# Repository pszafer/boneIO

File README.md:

# Project description

`BoneIO` is a compact IO controller for home automation. Main features of this controller are

- Compact size (27x11x6)cm - 15 DIN modules
- DIN rail compatibility
- Low price
- Open HSP (See below)

## Whole documentation you will find here: https://boneio.eu/

## Case, Circuit and Code was moved into separate repositories. You can find it here: https://github.com/boneIO-eu

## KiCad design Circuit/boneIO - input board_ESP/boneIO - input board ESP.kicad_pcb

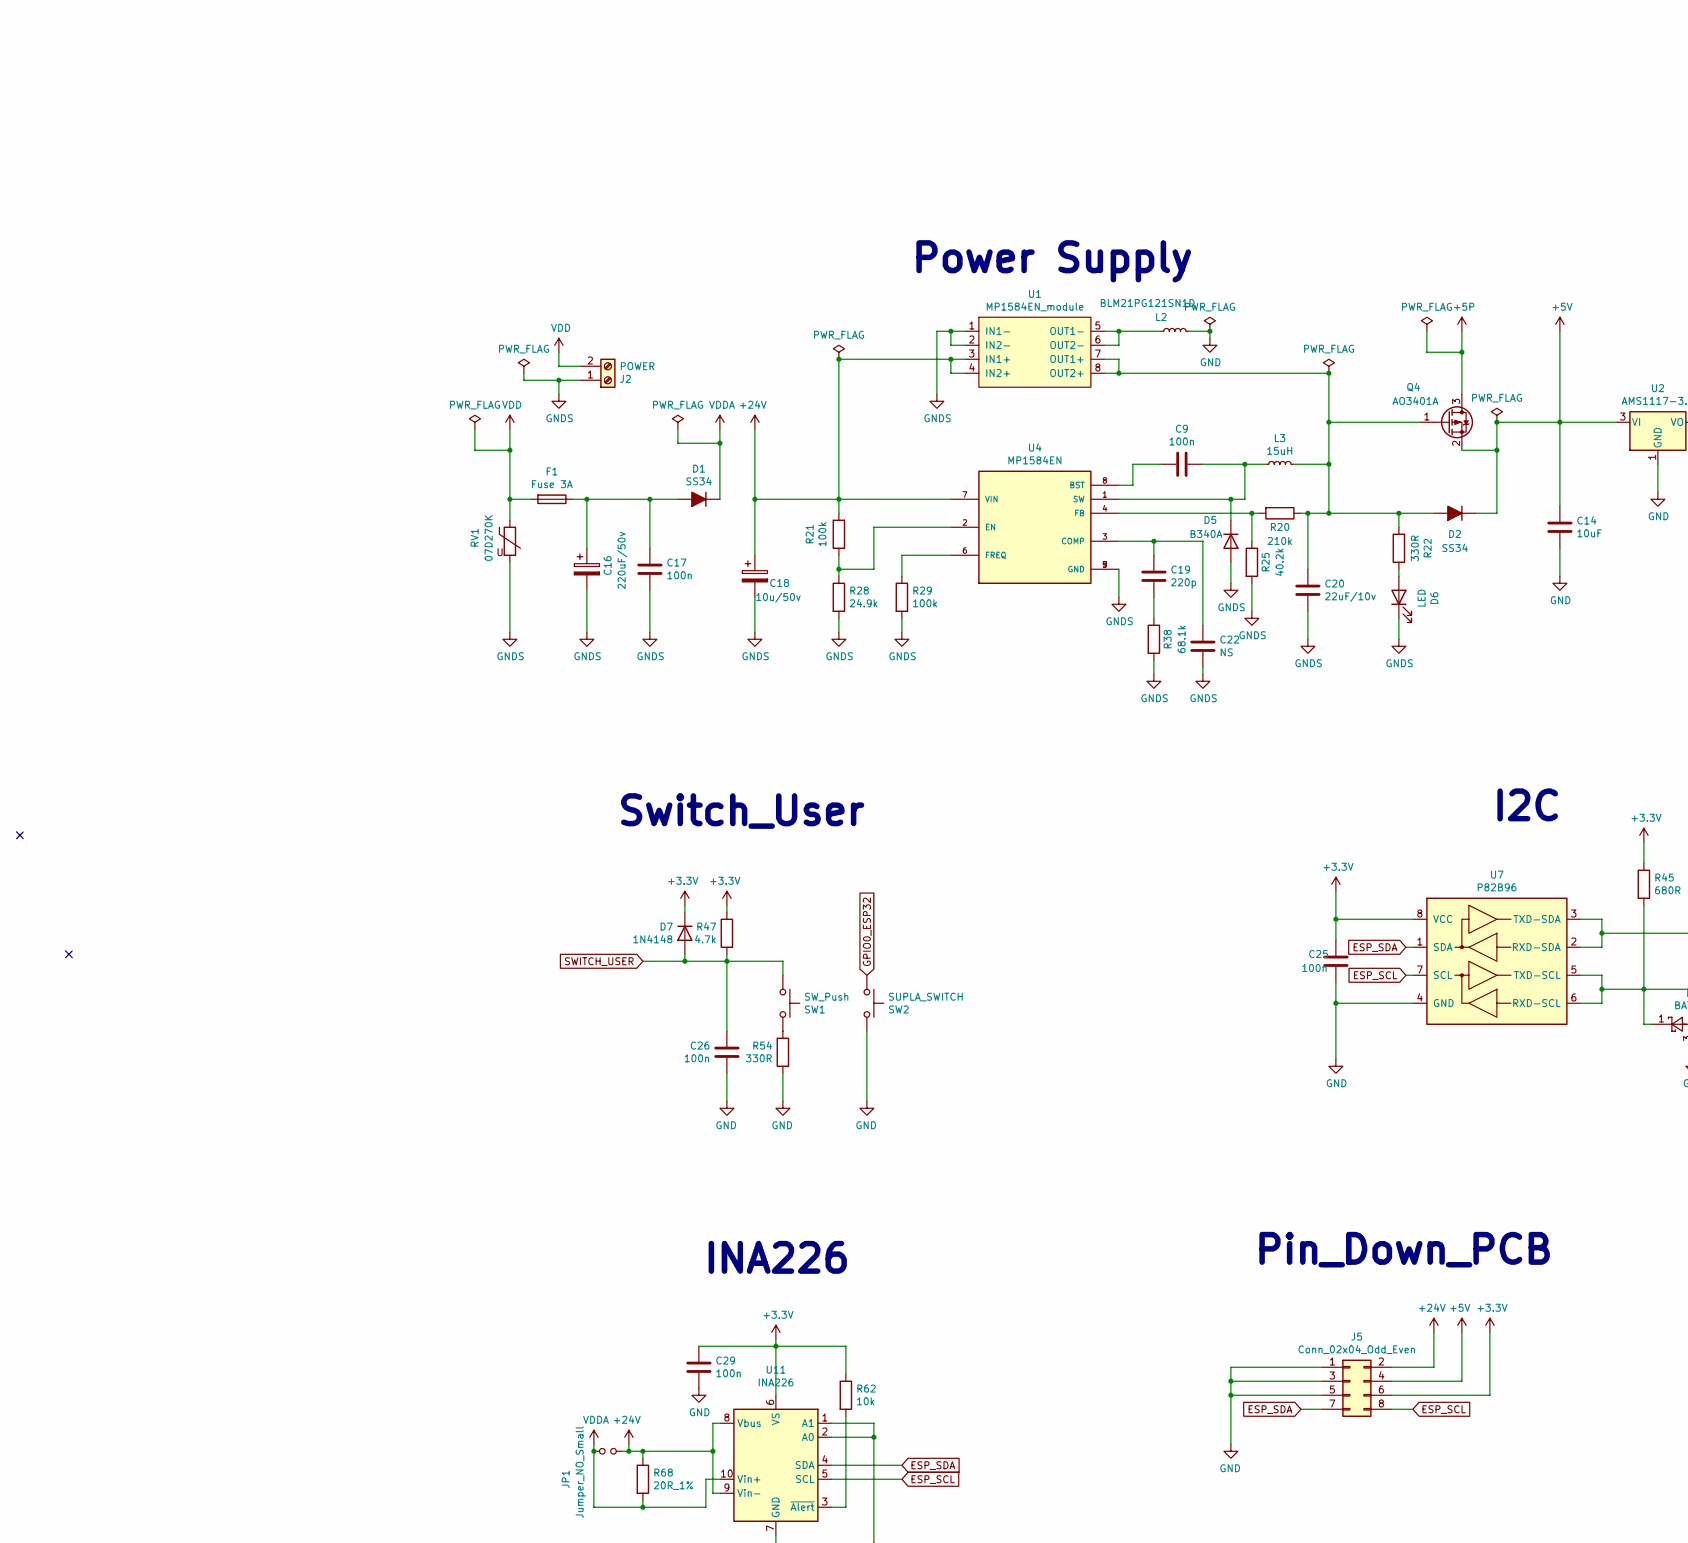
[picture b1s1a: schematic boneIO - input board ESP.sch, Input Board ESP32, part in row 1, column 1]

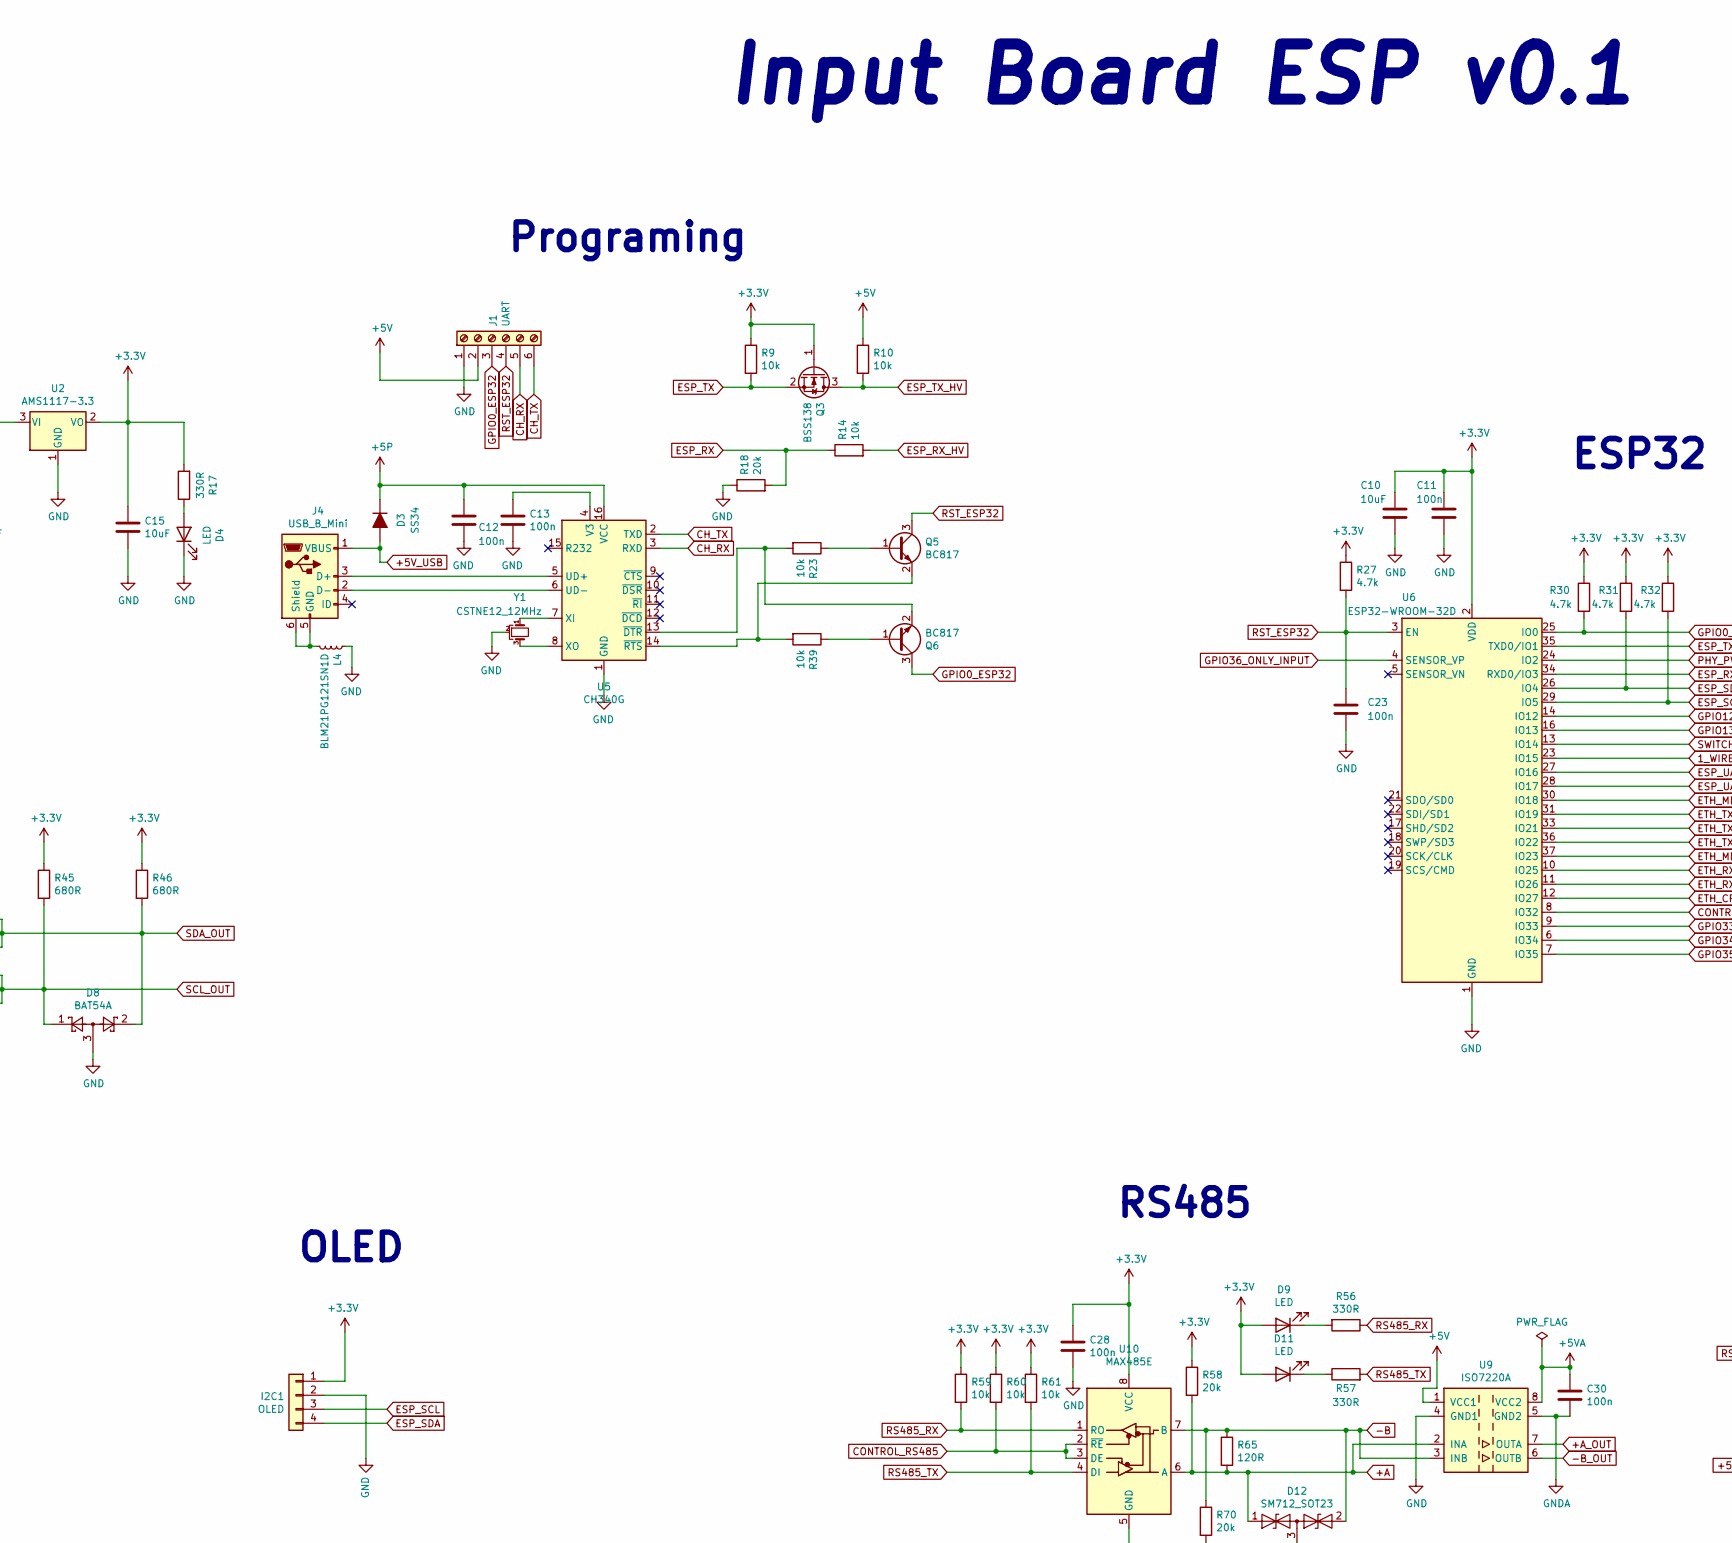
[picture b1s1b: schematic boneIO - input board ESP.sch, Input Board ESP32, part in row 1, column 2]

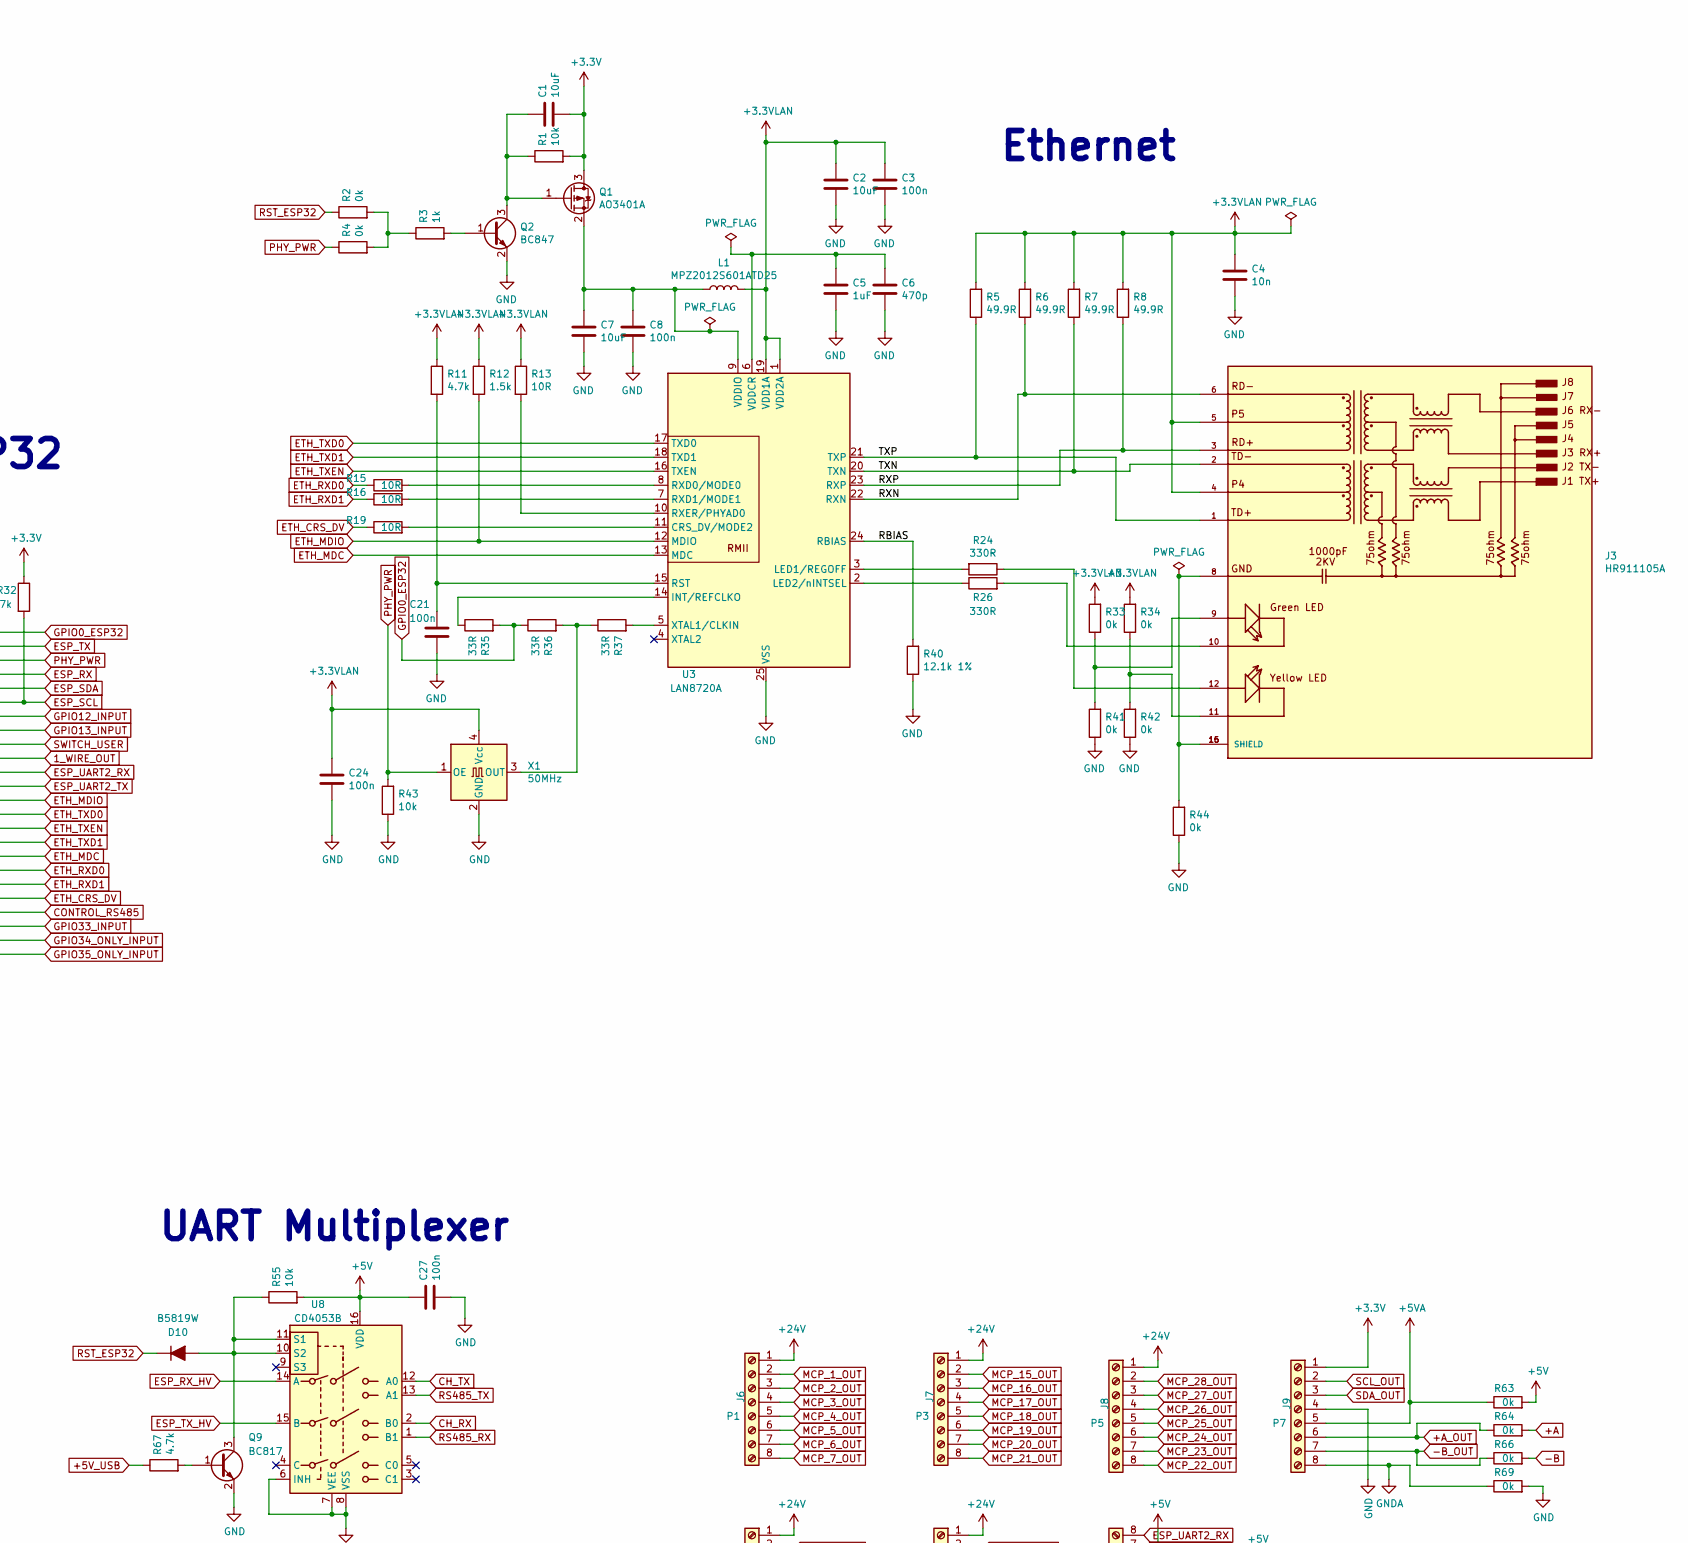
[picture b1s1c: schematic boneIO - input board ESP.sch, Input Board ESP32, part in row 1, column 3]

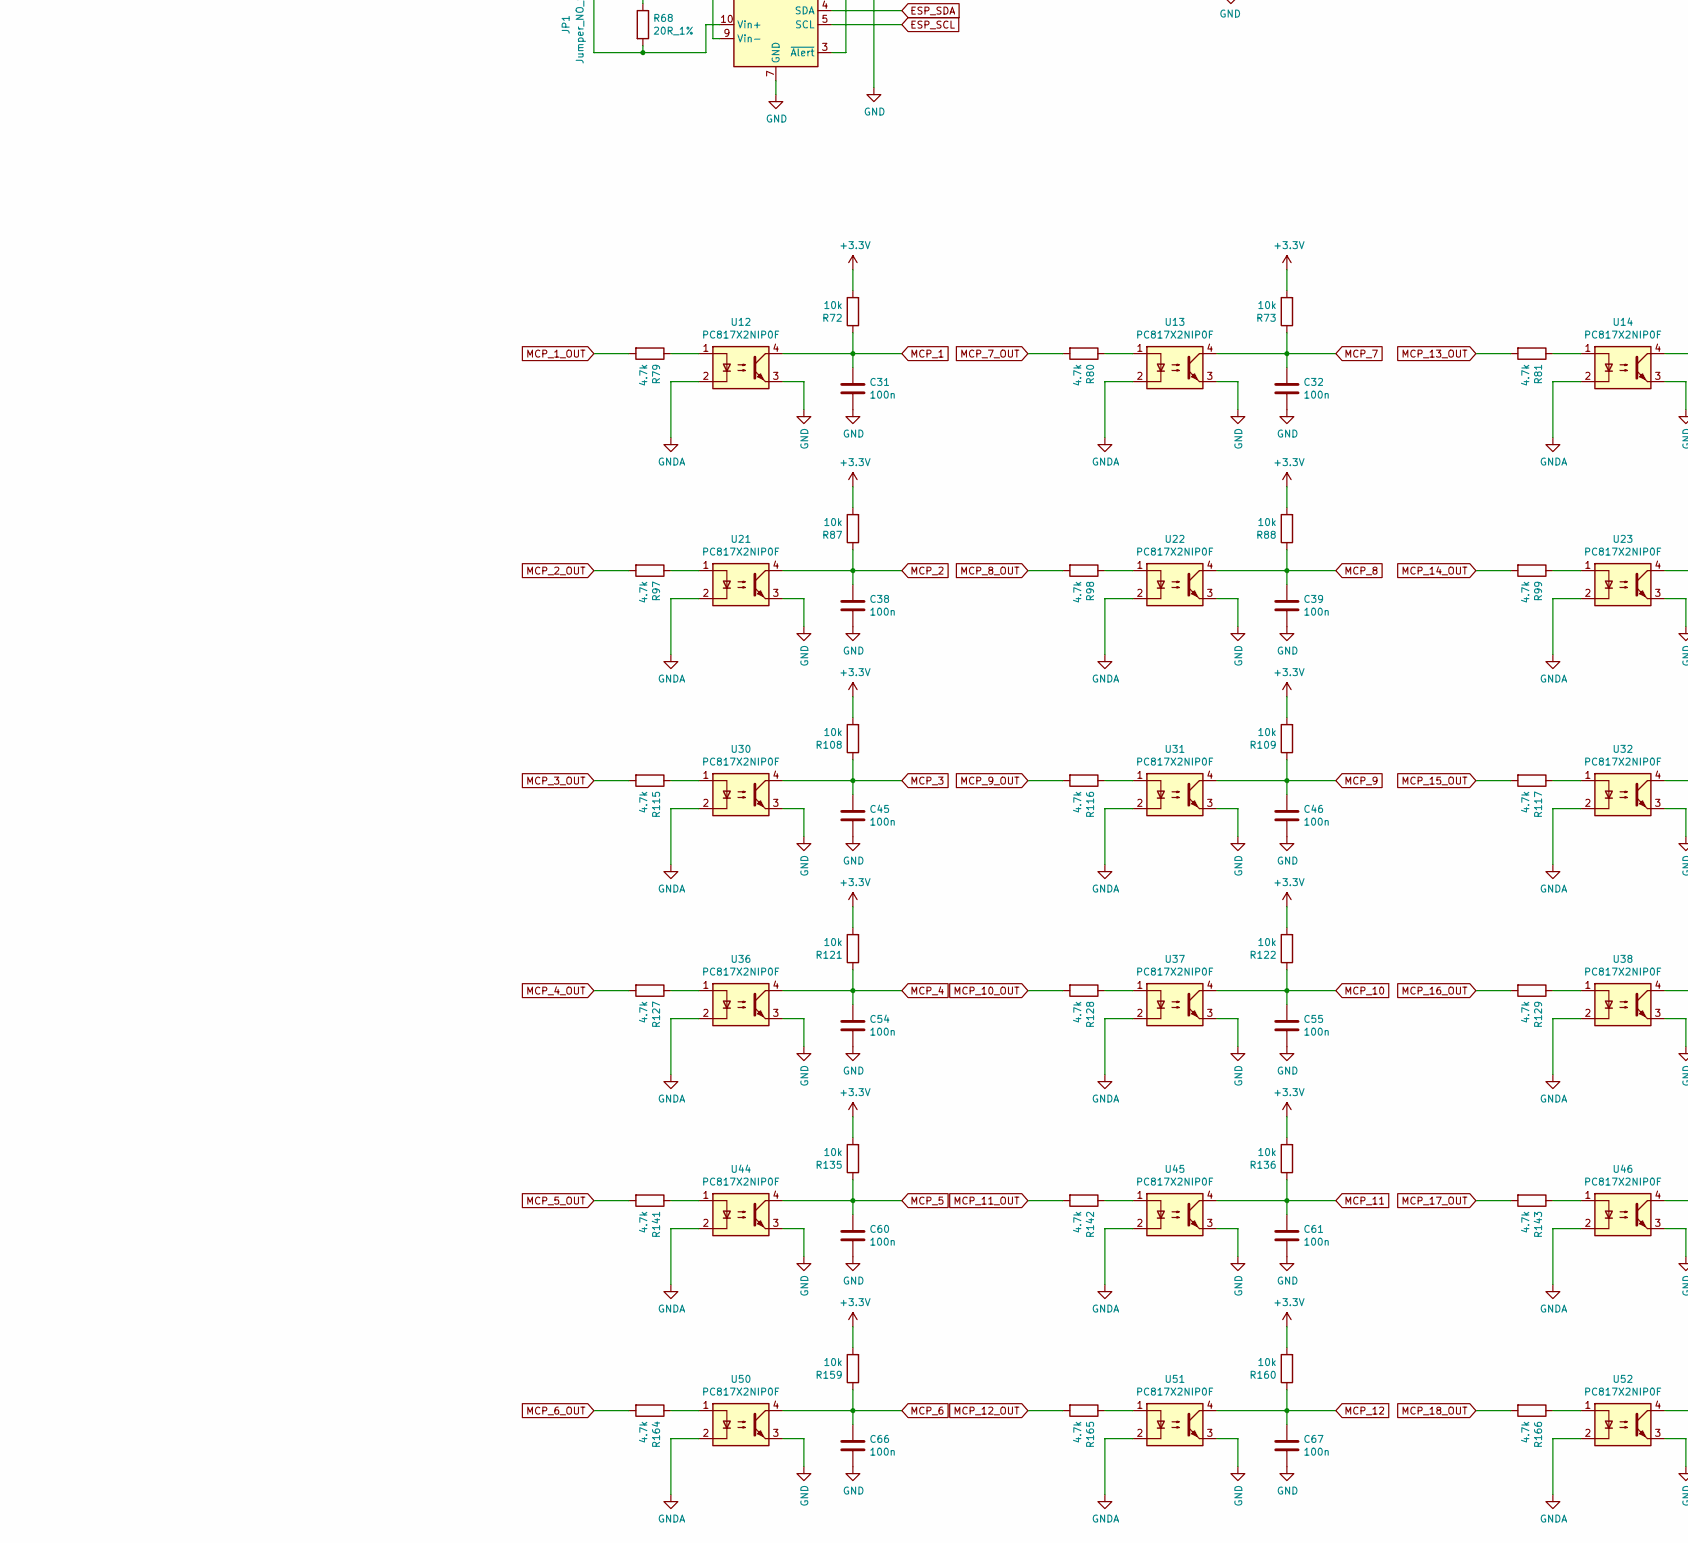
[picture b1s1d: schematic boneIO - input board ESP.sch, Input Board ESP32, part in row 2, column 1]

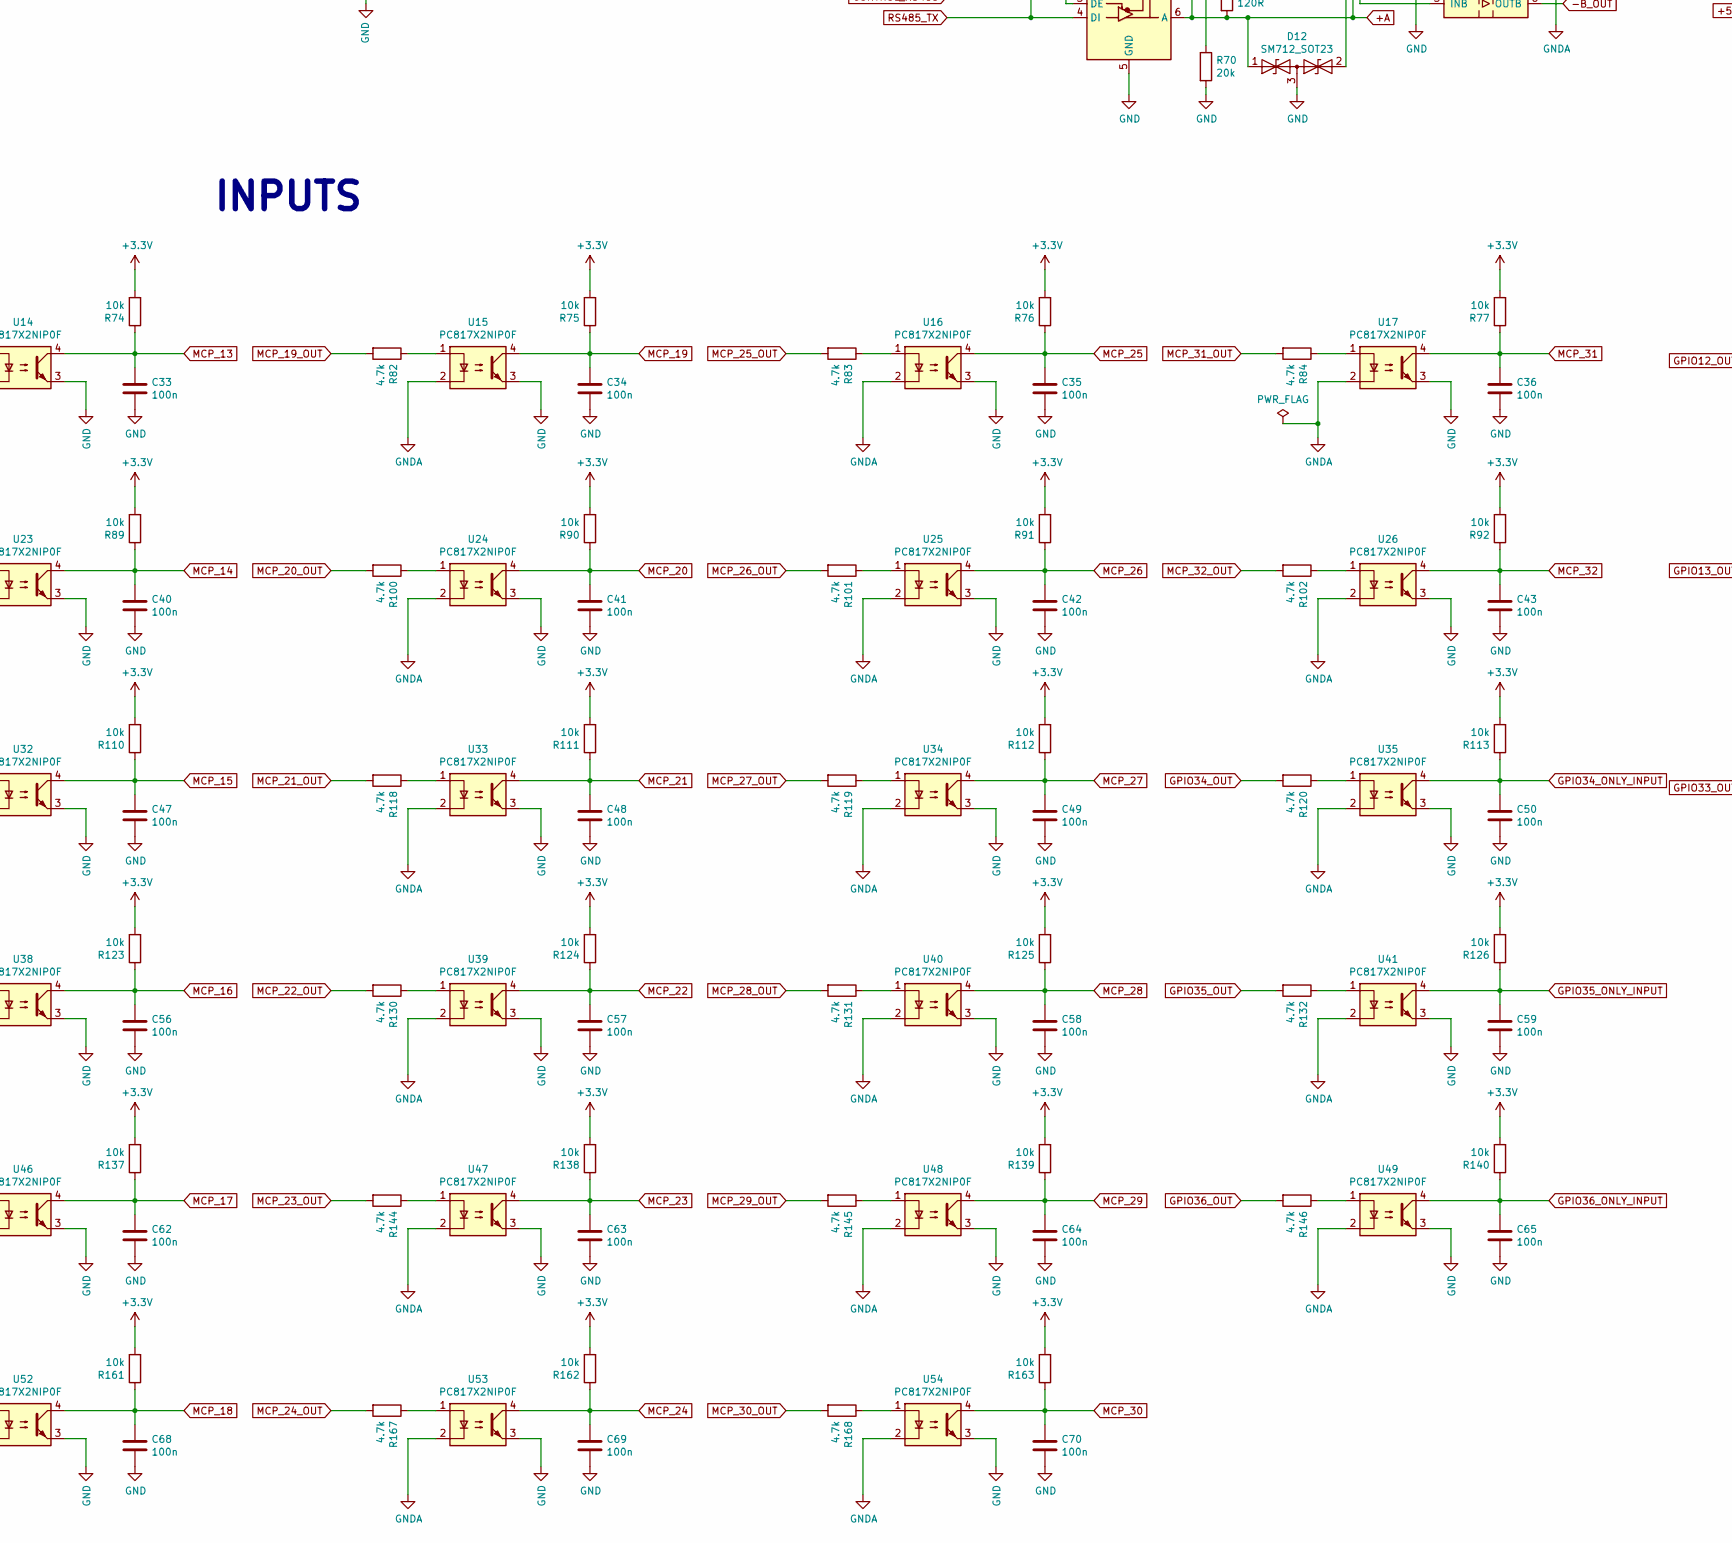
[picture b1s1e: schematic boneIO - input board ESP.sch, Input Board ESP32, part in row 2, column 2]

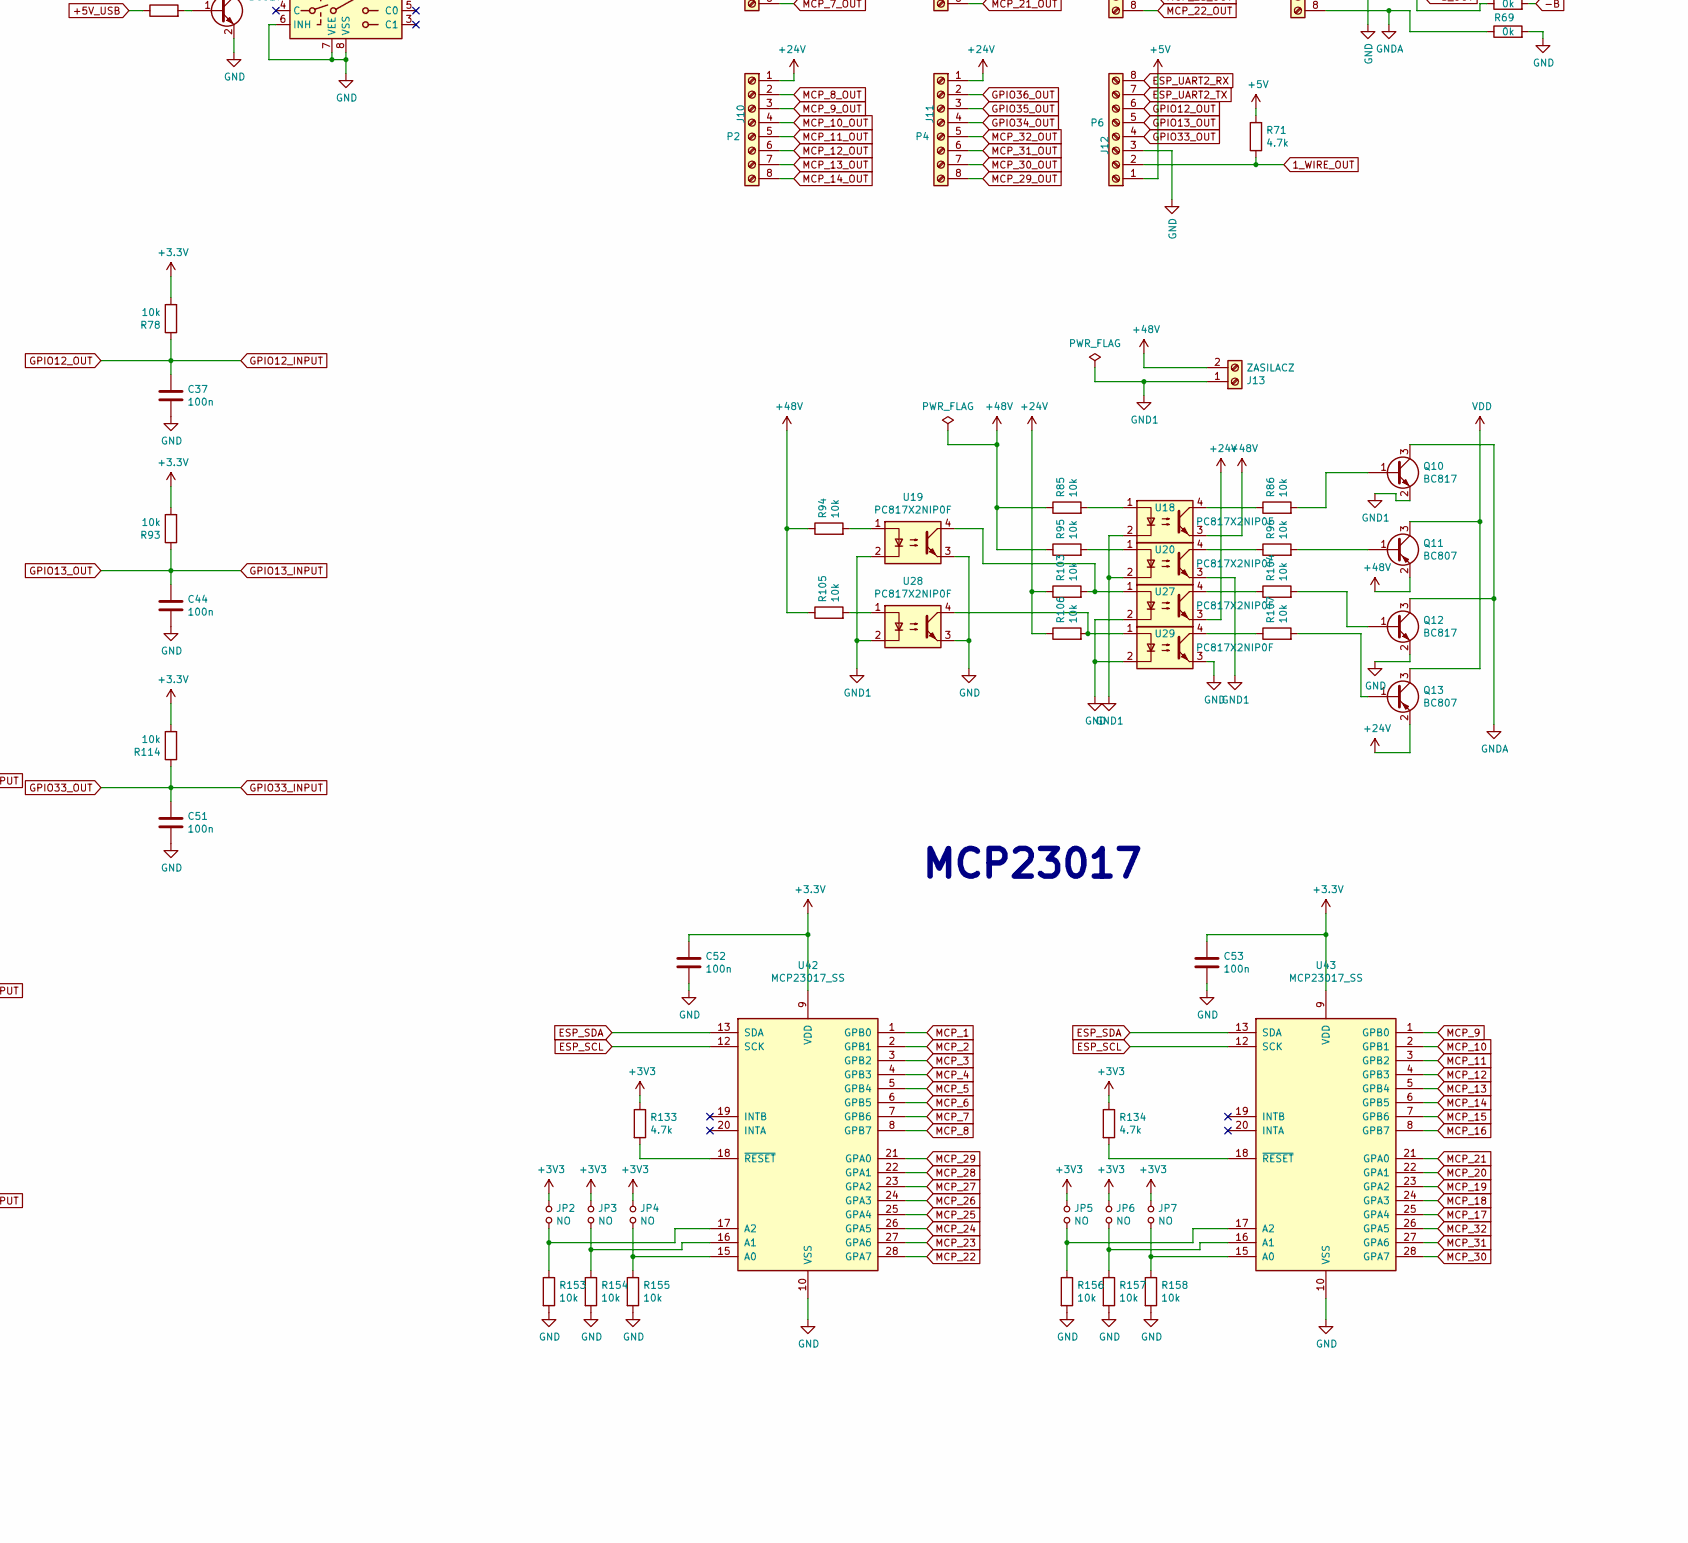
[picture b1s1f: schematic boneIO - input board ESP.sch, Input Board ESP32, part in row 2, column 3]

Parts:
C1, C2, C7, C10, C14, C15: 10uF; C_0805_2012Metric
C3, C8, C11, C12, C13, C17, C21, C23, C24, C27, C28, C29, C30, C52, C53: 100n; C_0603_1608Metric
C4: 10n; C_0805_2012Metric
C5: 1uF; C_0805_2012Metric
C6: 470p; C_0603_1608Metric
C9: 100n; C_0805_2012Metric
C16: 220uF/50v; CP_Elec_8x10
C18: 10u/50v; C_1206_3216Metric
C19: 220p; C_0603_1608Metric
C20: 22uF/10v; C_1206_3216Metric
C22: NS; C_0805_2012Metric
C25, C26, C31, C32, C33, C34, C35, C36, C37, C38, C39, C40, C41, C42, C43, C44, C45, C46, C47, C48, C49, C50, C51, C54, C55, C56, C57, C58, C59, C60, C61, C62, C63, C64, C65, C66, C67, C68, C69, C70: 100n; C_0603_1608Metric; JLCPCB C14663
D1: SS34; D_SMA; JLCPCB C64982
D2, D3: SS34; D_SOD-323_HandSoldering; JLCPCB C64982
D4, D6, D9, D11: LED; C_0805_2012Metric
D5: B340A; D_SMA
D7: 1N4148; D_MiniMELF; JLCPCB C68883
D8: BAT54A; SOT-23; JLCPCB C466636
D10: B5819W; D_SMA; JLCPCB C64982
D12: SM712_SOT23; SOT-23
F1: Fuse 3A; Fuse_2512_6332Metric
I2C1: OLED; PinSocket_1x04_P2.54mm_Vertical
J1: UART; PinHeader_1x06_P2.00mm_Vertical
J2: POWER; pin2
J3: HR911105A; HANRUN_HR911105A; PARTREV A
J4: USB_B_Mini; USB_Mini-B_Wuerth_65100516121_Horizontal
J5: Conn_02x04_Odd_Even; PinHeader_2x04_P2.54mm_Vertical
J6: P1; pin8
J7: P3; pin8
J8: P5; pin8
J9: P7; pin8
J10: P2; pin8
J11: P4; pin8
J12: P6; pin8
J13: ZASILACZ; pin2
JP1: Jumper_NO_Small; SolderJumper-2_P1.3mm_Open_RoundedPad1.0x1.5mm
JP2, JP3, JP4, JP5, JP6, JP7: NO; SolderJumper-2_P1.3mm_Open_RoundedPad1.0x1.5mm
L1: MPZ2012S601ATD25; L_0805_2012Metric
L2, L4: BLM21PG121SN1D; L_0805_2012Metric
L3: 15uH; L_7.3x7.3_H4.5
Q1, Q4: AO3401A; SOT-23
Q2: BC847; SOT-23
Q3: BSS138; SOT-23
Q5, Q6, Q9, Q10, Q12: BC817; SOT-23
Q11, Q13: BC807; SOT-23
R1, R9, R10, R14, R23, R39, R43, R153, R154, R155, R156, R157, R158: 10k; R_0603_1608Metric
R2, R4, R33, R34, R41, R42, R44, R63, R64, R66, R69: 0k; R_0603_1608Metric
R3: 1k; R_0603_1608Metric
R5, R6, R7, R8: 49.9R; R_0603_1608Metric
R11, R27, R30, R31, R32, R71, R133, R134: 4.7k; R_0603_1608Metric
R12: 1.5k; R_0603_1608Metric
R13, R15, R16, R19: 10R; R_0603_1608Metric
R17, R22, R24, R26, R56, R57: 330R; R_0603_1608Metric
R18: 20k; R_0603_1608Metric
R20: 210k; R_0603_1608Metric
R21, R29: 100k; R_0603_1608Metric
R25: 40.2k; R_0603_1608Metric
R28: 24.9k; R_0603_1608Metric
R35, R36, R37: 33R; R_0603_1608Metric
R38: 68.1k; R_0603_1608Metric
R40: 12.1k 1%; R_0603_1608Metric
R45, R46: 680R; R_0603_1608Metric; JLCPCB C269704
R47, R79, R80, R81, R82, R83, R84, R97, R98, R99, R100, R101, R102, R115, R116, R117, R118, R119, R120, R127, R128, R129, R130, R131, R132, R141, R142, R143, R144, R145, R146, R164, R165, R166, R167, R168: 4.7k; R_0603_1608Metric; JLCPCB C237118
R54: 330R; R_0603_1608Metric; JLCPCB C101062
R55, R59, R60, R61, R62: 10k; R_0603_1608Metric; JLCPCB C269704
R58, R70: 20k; R_0603_1608Metric; JLCPCB C269704
R65: 120R; R_0603_1608Metric; JLCPCB C269704
R67: 4.7k; R_0603_1608Metric; JLCPCB C269704
R68: 20R_1%; R_2512_6332Metric
R72, R73, R74, R75, R76, R77, R78, R85, R86, R87, R88, R89, R90, R91, R92, R93, R94, R95, R96, R103, R104, R105, R106, R107, R108, R109, R110, R111, R112, R113, R114, R121, R122, R123, R124, R125, R126, R135, R136, R137, R138, R139, R140, R159, R160, R161, R162, R163: 10k; R_0603_1608Metric; JLCPCB C238881
RV1: 07D270K; RV_Disc_D7mm_W3.5mm_P5mm; JLCPCB C317745
SW1: SW_Push; SW_PUSH_6mm_H13mm
SW2: SUPLA_SWITCH; SW_Tactile_SPST_Angled_PTS645Vx39-2LFS
U1: MP1584EN_module; MP1584-_module
U2: AMS1117-3.3; SOT-223-3_TabPin2
U3: LAN8720A; QFN-24-1EP_4x4mm_P0.5mm_EP2.6x2.6mm
U4: MP1584EN; SOIC127P600X170-9N
U5: CH340G; SOIC-16_3.9x9.9mm_P1.27mm
U6: ESP32-WROOM-32D; ESP32-WROOM-32
U7: P82B96; SO-8_3.9x4.9mm_P1.27mm; JLCPCB C32103
U8: CD4053B; SOIC-16W_5.3x10.2mm_P1.27mm
U9: ISO7220A; SOIC-8_3.9x4.9mm_P1.27mm
U10: MAX485E; SOP-8_3.9x4.9mm_P1.27mm
U11: INA226; VSSOP-10_3x3mm_P0.5mm
U12, U13, U14, U15, U16, U17, U18, U19, U20, U21, U22, U23, U24, U25, U26, U27, U28, U29, U30, U31, U32, U33, U34, U35, U36, U37, U38, U39, U40, U41, U44, U45, U46, U47, U48, U49, U50, U51, U52, U53, U54: PC817X2NIP0F; SOT254P975X400-4N; JLCPCB C6649
U42, U43: MCP23017_SS; SSOP-28_5.3x10.2mm_P0.65mm
X1: 50MHz; Oscillator_SMD_EuroQuartz_XO91-4Pin_7.0x5.0mm_HandSoldering
Y1: CSTNE12_12MHz; Resonator_SMD_muRata_CSTxExxV-3Pin_3.0x1.1mm

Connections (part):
1_WIRE_OUT: J12.2, R71.1, U6.23 (IO15)
+3.3VLAN: C2.1, C3.1, C4.1, C24.1, J3.4, J3.5, L1.2, R5.2, R6.2, R7.2, R8.2, R11.1, R12.1, R13.1, R33.2, R34.2, U3.1 (VDD2A), U3.19 (VDD1A), X1.4 (Vcc)
+5P: C12.1, D3.1 (K), Q4.3 (D), U5.16 (VCC)
+5V: C14.1, C27.1, D2.1 (K), J1.2, J5.4, J12.1, Q4.2 (S), R10.1, R55.2, R63.2, R71.2, U2.3 (VI), U8.16 (VDD), U9.1 (VCC1)
+5VA: C30.1, J9.5, R63.1, U9.8 (VCC2)
+5V_USB: D3.2 (A), J4.1 (VBUS), R67.1
+24V: C18.1, J5.2, J6.1, J7.1, J8.1, J10.1, J11.1, JP1.2, Q13.2 (E), R21.2, R68.1, R103.1, R106.1, U1.3 (IN1+), U1.4 (IN2+), U4.7 (VIN), U11.8 (Vbus), U11.9 (Vin-), U27.3
+48V: J13.2, Q11.2 (E), R85.1, R94.1, R95.1, R105.1, U18.3
+A: D12.1 (A1), R58.2, R64.2, R65.2, U9.2 (INA), U10.6 (A)
+A_OUT: J9.6, R64.1, U9.7 (OUTA)
-B: D12.2 (A2), R65.1, R66.2, R70.1, U9.3 (INB), U10.7 (B)
-B_OUT: J9.7, R66.1, U9.6 (OUTB)
/RBIAS: R40.2, U3.24 (RBIAS)
/RXN: J3.6, R6.1, U3.22 (RXN)
/RXP: J3.3, R8.1, U3.23 (RXP)
/TXN: J3.2, R7.1, U3.20 (TXN)
/TXP: J3.1, R5.1, U3.21 (TXP)
CH_RX: J1.5, U5.3 (RXD), U8.2 (B0)
CH_TX: J1.6, U5.2 (TXD), U8.12 (A0)
CONTROL_RS485: R60.2, U6.8 (IO32), U10.2 (~RE), U10.3 (DE)
ESP_RX: R14.1, R18.2, U6.34 (RXD0/IO3)
ESP_RX_HV: R14.2, U8.14 (A)
ESP_SCL: I2C1.3, J5.8, R32.2, U6.29 (IO5), U7.7 (SCL), U11.5 (SCL), U42.12 (SCK), U43.12 (SCK)
ESP_SDA: I2C1.4, J5.7, R31.2, U6.26 (IO4), U7.1 (SDA), U11.4 (SDA), U42.13 (SDA), U43.13 (SDA)
ESP_TX: Q3.2 (S), R9.2, U6.35 (TXD0/IO1)
ESP_TX_HV: Q3.3 (D), R10.2, U8.15 (B)
ESP_UART2_RX: J12.8, U6.27 (IO16)
ESP_UART2_TX: J12.7, U6.28 (IO17)
ETH_CRS_DV: R19.1, U6.12 (IO27)
ETH_MDC: U3.13 (MDC), U6.37 (IO23)
ETH_MDIO: R12.2, U3.12 (MDIO), U6.30 (IO18)
ETH_RXD0: R15.1, U6.10 (IO25)
ETH_RXD1: R16.1, U6.11 (IO26)
ETH_TXD0: U3.17 (TXD0), U6.31 (IO19)
ETH_TXD1: U3.18 (TXD1), U6.36 (IO22)
ETH_TXEN: U3.16 (TXEN), U6.33 (IO21)
GND: C2.2, C3.2, C4.2, C5.2, C6.2, C7.2, C8.2, C10.2, C11.2, C12.2, C13.2, C14.2, C15.2, C21.2, C23.2, C24.2, C25.2, C26.2, C27.2, C28.2, C29.2, C31.2, C32.2, C33.2, C34.2, C35.2, C36.2, C37.2, C38.2, C39.2, C40.2, C41.2, C42.2, C43.2, C44.2, C45.2, C46.2, C47.2, C48.2, C49.2, C50.2, C51.2, C52.2, C53.2, C54.2, C55.2, C56.2, C57.2, C58.2, C59.2, C60.2, C61.2, C62.2, C63.2, C64.2, C65.2, C66.2, C67.2, C68.2, C69.2, C70.2, D4.1 (K), D8.3, D12.3 (common), I2C1.2, J1.1, J5.1, J5.3, J5.5, J9.4, J12.3, L2.2, L4.1, Q2.2 (E), Q9.2 (E), Q12.2 (E), R18.1, R40.1, R41.1, R42.1, R43.1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
GND1: J13.1, Q10.2 (E), U18.2, U19.2, U20.2, U20.3, U28.2
GNDA: C30.2, J9.8, Q10.3 (C), Q12.3 (C), R69.1, U9.5 (GND2), U12.2, U13.2, U14.2, U15.2, U16.2, U17.2, U21.2, U22.2, U23.2, U24.2, U25.2, U26.2, U30.2, U31.2, U32.2, U33.2, U34.2, U35.2, U36.2, U37.2, U38.2, U39.2, U40.2, U41.2, U44.2, U45.2, U46.2, U47.2, U48.2, U49.2, U50.2, U51.2, U52.2, U53.2, U54.2
GNDS: C16.2, C17.2, C18.2, C20.2, C22.2, D5.2 (A), D6.1 (K), J2.1, R25.2, R28.2, R29.2, R38.2, RV1.2, U1.1 (IN1-), U1.2 (IN2-), U4.5 (GND), U4.9 (GND)
GPIO0_ESP32: J1.3, Q6.3 (C), R30.2, R35.2, R36.1, SW2.2, U6.25 (IO0)
GPIO12_INPUT: C37.1, J12.6, R78.1, U6.14 (IO12)
GPIO13_INPUT: C44.1, J12.5, R93.1, U6.16 (IO13)
GPIO33_INPUT: C51.1, J12.4, R114.1, U6.9 (IO33)
GPIO34_ONLY_INPUT: C50.1, R113.1, U6.6 (IO34), U35.4
GPIO34_OUT: J11.4, R120.2
GPIO35_ONLY_INPUT: C59.1, R126.1, U6.7 (IO35), U41.4
GPIO35_OUT: J11.3, R132.2
GPIO36_ONLY_INPUT: C65.1, R140.1, U6.4 (SENSOR_VP), U49.4
GPIO36_OUT: J11.2, R146.2
MCP_1: C31.1, R72.1, U12.4, U42.1 (GPB0)
MCP_1_OUT: J6.2, R79.2
MCP_2: C38.1, R87.1, U21.4, U42.2 (GPB1)
MCP_2_OUT: J6.3, R97.2
MCP_3: C45.1, R108.1, U30.4, U42.3 (GPB2)
MCP_3_OUT: J6.4, R115.2
MCP_4: C54.1, R121.1, U36.4, U42.4 (GPB3)
MCP_4_OUT: J6.5, R127.2
MCP_5: C60.1, R135.1, U42.5 (GPB4), U44.4
MCP_5_OUT: J6.6, R141.2
MCP_6: C66.1, R159.1, U42.6 (GPB5), U50.4
MCP_6_OUT: J6.7, R164.2
MCP_7: C32.1, R73.1, U13.4, U42.7 (GPB6)
MCP_7_OUT: J6.8, R80.2
MCP_8: C39.1, R88.1, U22.4, U42.8 (GPB7)
MCP_8_OUT: J10.2, R98.2
MCP_9: C46.1, R109.1, U31.4, U43.1 (GPB0)
MCP_9_OUT: J10.3, R116.2
MCP_10: C55.1, R122.1, U37.4, U43.2 (GPB1)
MCP_10_OUT: J10.4, R128.2
MCP_11: C61.1, R136.1, U43.3 (GPB2), U45.4
MCP_11_OUT: J10.5, R142.2
MCP_12: C67.1, R160.1, U43.4 (GPB3), U51.4
MCP_12_OUT: J10.6, R165.2
MCP_13: C33.1, R74.1, U14.4, U43.5 (GPB4)
MCP_13_OUT: J10.7, R81.2
MCP_14: C40.1, R89.1, U23.4, U43.6 (GPB5)
MCP_14_OUT: J10.8, R99.2
MCP_15: C47.1, R110.1, U32.4, U43.7 (GPB6)
MCP_15_OUT: J7.2, R117.2
MCP_16: C56.1, R123.1, U38.4, U43.8 (GPB7)
MCP_16_OUT: J7.3, R129.2
MCP_17: C62.1, R137.1, U43.25 (GPA4), U46.4
MCP_17_OUT: J7.4, R143.2
MCP_18: C68.1, R161.1, U43.24 (GPA3), U52.4
MCP_18_OUT: J7.5, R166.2
MCP_19: C34.1, R75.1, U15.4, U43.23 (GPA2)
MCP_19_OUT: J7.6, R82.2
MCP_20: C41.1, R90.1, U24.4, U43.22 (GPA1)
MCP_20_OUT: J7.7, R100.2
MCP_21: C48.1, R111.1, U33.4, U43.21 (GPA0)
MCP_21_OUT: J7.8, R118.2
MCP_22: C57.1, R124.1, U39.4, U42.28 (GPA7)
MCP_22_OUT: J8.8, R130.2
MCP_23: C63.1, R138.1, U42.27 (GPA6), U47.4
MCP_23_OUT: J8.7, R144.2
MCP_24: C69.1, R162.1, U42.26 (GPA5), U53.4
MCP_24_OUT: J8.6, R167.2
MCP_25: C35.1, R76.1, U16.4, U42.25 (GPA4)
MCP_25_OUT: J8.5, R83.2
MCP_26: C42.1, R91.1, U25.4, U42.24 (GPA3)
MCP_26_OUT: J8.4, R101.2
MCP_27: C49.1, R112.1, U34.4, U42.23 (GPA2)
MCP_27_OUT: J8.3, R119.2
MCP_28: C58.1, R125.1, U40.4, U42.22 (GPA1)
MCP_28_OUT: J8.2, R131.2
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
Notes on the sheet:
INA226
Switch_User
RS485
I2C
Pin_Down_PCB
OLED
MCP23017
Ethernet
ESP32
INPUTS
Input Board ESP v0.1
UART Multiplexer
Power Supply
Programing

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
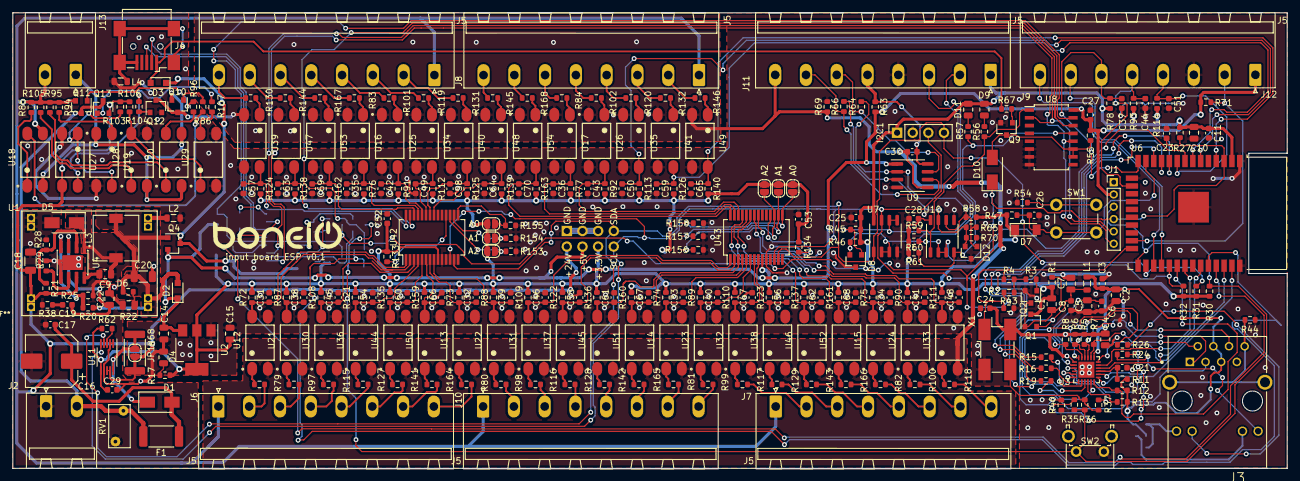
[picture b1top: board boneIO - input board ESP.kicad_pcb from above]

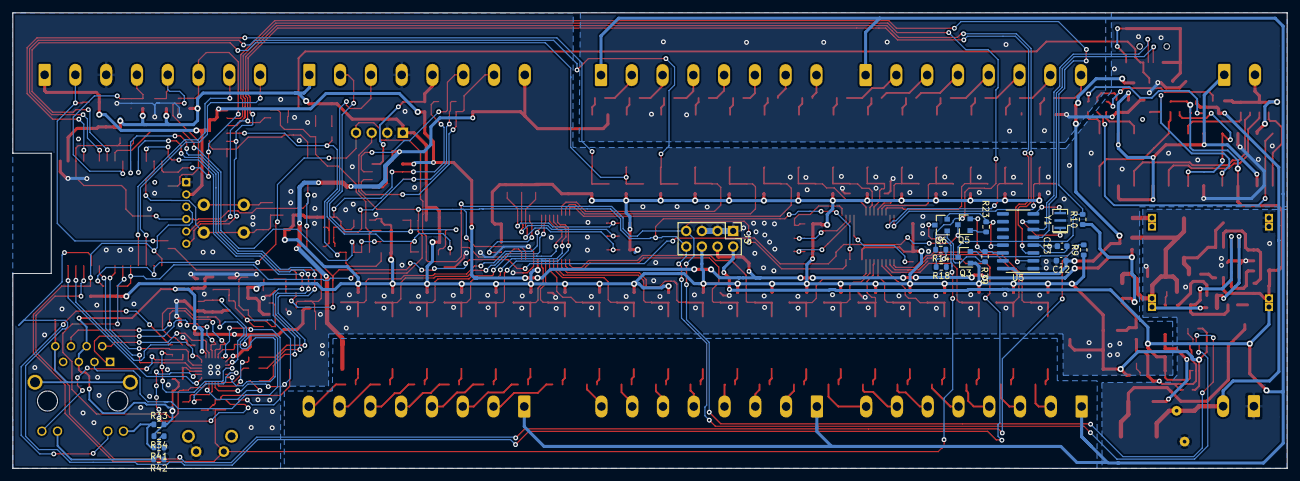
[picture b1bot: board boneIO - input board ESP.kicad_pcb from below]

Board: 2 copper layers, 207.0 x 74.0 mm, 334 parts (18 on the bottom side), 229 nets.

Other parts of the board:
A0, A0#2, A1, A1#2, A2, A2#2: NO; SolderJumper-2_P1.3mm_Open_RoundedPad1.0x1.5mm

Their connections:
unnamed 139: A2#2.2; also elsewhere on the board
unnamed 140: A1#2.2; also elsewhere on the board
unnamed 141: A0#2.2; also elsewhere on the board
unnamed 142: A2.2; also elsewhere on the board
unnamed 143: A1.2; also elsewhere on the board
unnamed 144: A0.2; also elsewhere on the board
